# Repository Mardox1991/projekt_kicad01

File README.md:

# projekt_kicad01
4 layer universal pcb atmega328p ( first pcb project )

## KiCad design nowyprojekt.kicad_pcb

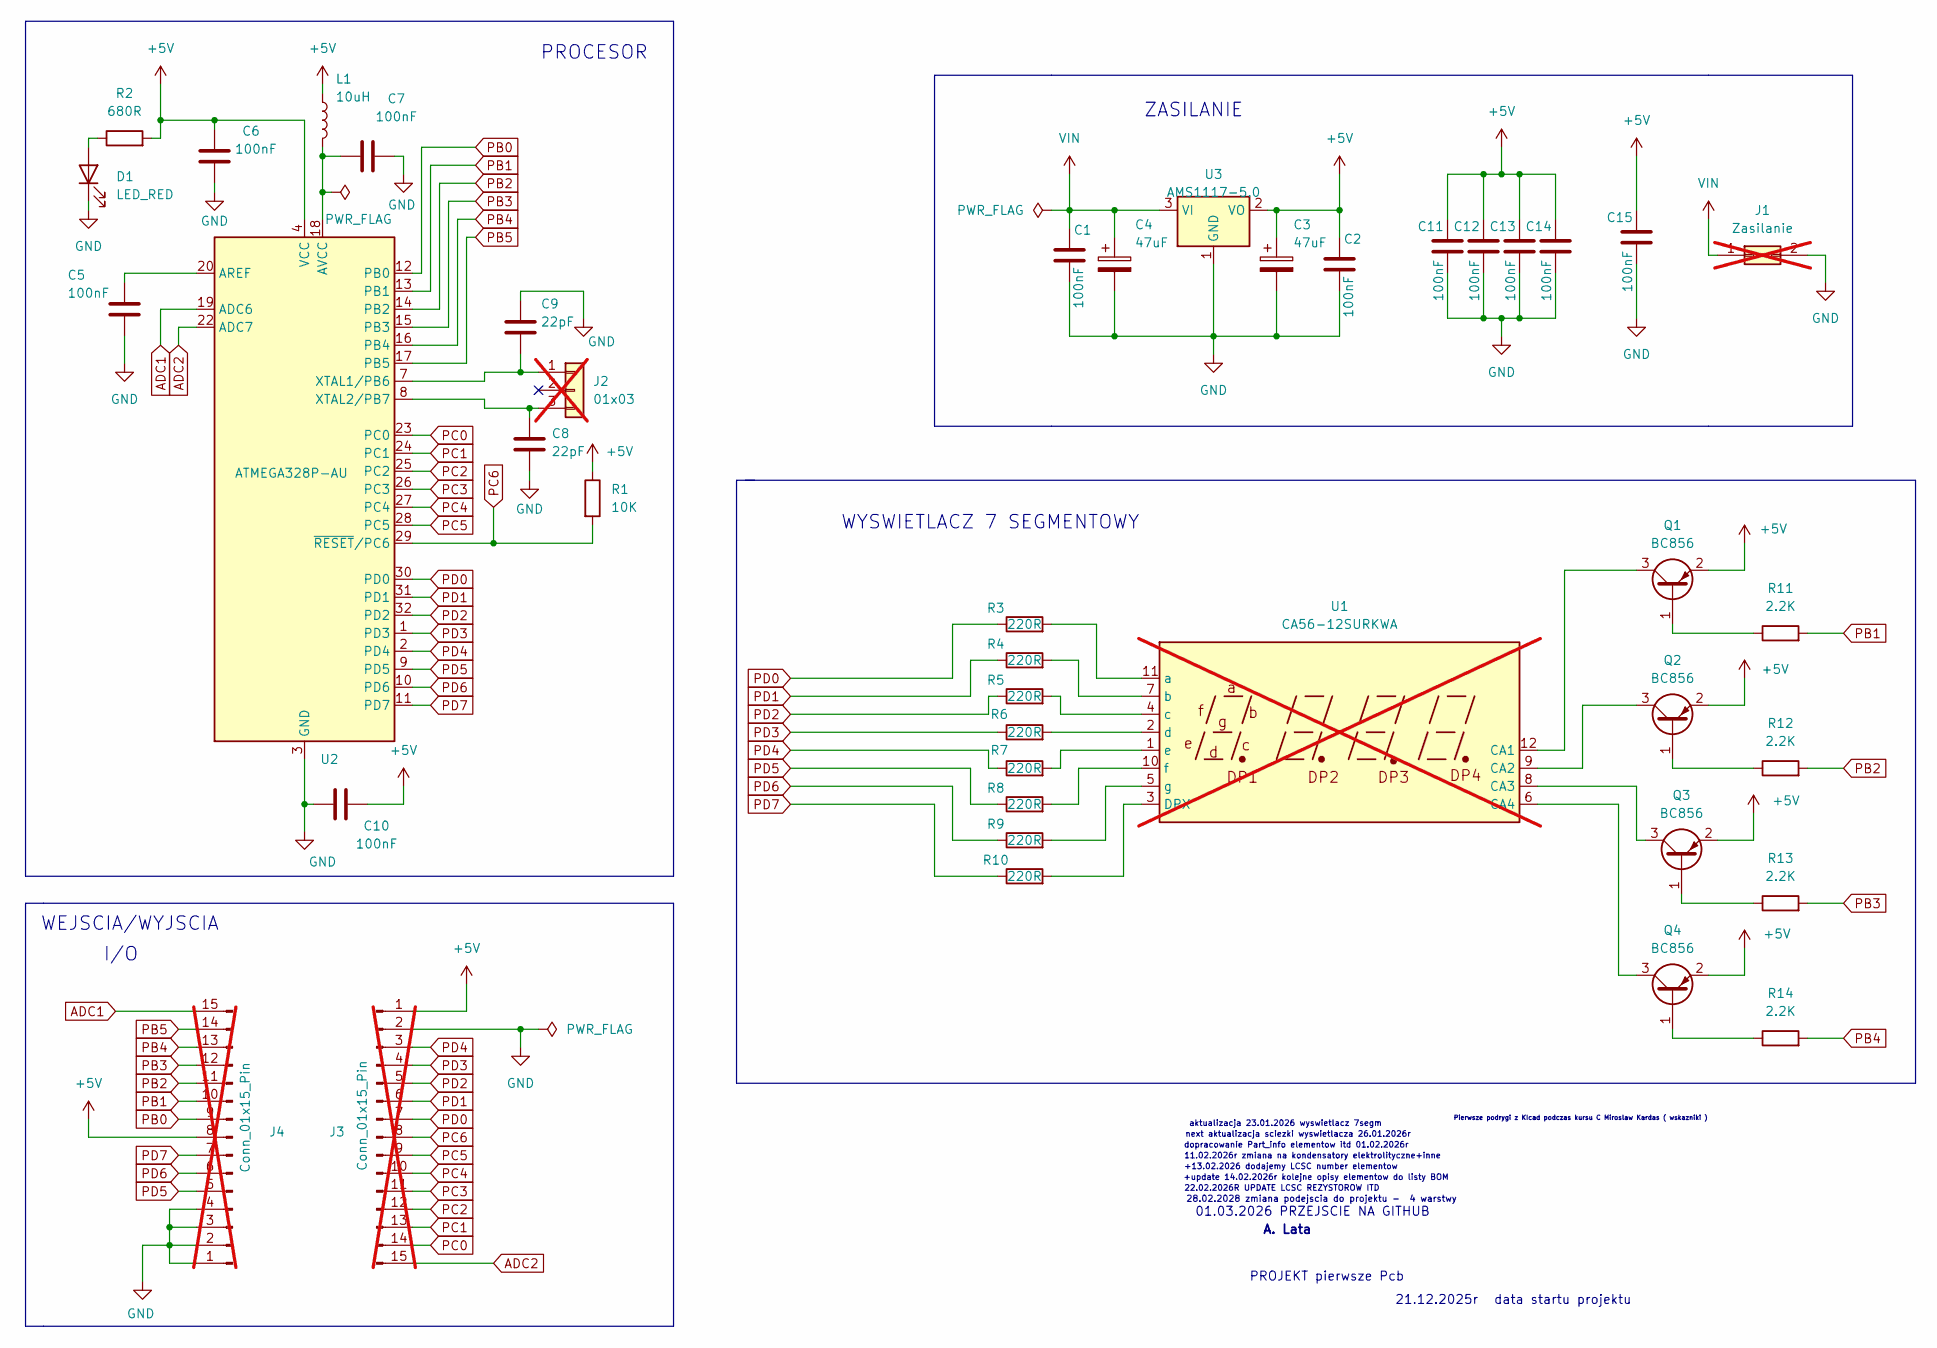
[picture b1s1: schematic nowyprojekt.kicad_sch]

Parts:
C1, C2, C5, C6, C7, C10, C11, C12, C13, C14, C15: 100nF; C_0603_1608Metric; Part_info Ceramic Capacitor 100nF 50V X7R 10%; LCSC C14663
C3, C4: 47uF; CP_Elec_8x6.2; Part_info 47µF, Low ESR, 50V DC, ±20%, -55...105°C; LCSC C278400
C8, C9: 22pF; C_0603_1608Metric; Part_info Ceramic Capacitor 22pF 50V C0G (NP0) 5%; LCSC C1653
D1: LED_RED; LED_0603_1608Metric; Part_info 20mA, 0603, Red, 2.4V, SMD; LCSC C2286
J1: Zasilanie; PinHeader_1x02_P2.54mm_Vertical; not fitted
J2: 01x03; PinHeader_1x03_P2.54mm_Vertical; not fitted
J3, J4: Conn_01x15_Pin; PinHeader_1x15_P2.54mm_Vertical; not fitted
L1: 10uH; L_1206_3216Metric; MPN CMP321609XD100MT; LCSC C395029
Q1, Q2, Q3, Q4: BC856; SOT-23; Part_info PNP, 65V, 0,1A, 0,25W, SMD; LCSC C108440
R1: 10K; R_0603_1608Metric; Part_info 10K, 0603, 1%, 0.1W, 75V; LCSC C25804
R2: 680R; R_0603_1608Metric; Part_info 0603, 680R, 1%, 0.1W, 75V; LCSC C23228
R3, R4, R5, R6, R7, R8, R9, R10: 220R; R_0603_1608Metric; Part_info 220R, 0603, 1%, 0.1W, 75V; LCSC C22962
R11, R12, R13, R14: 2.2K; R_0603_1608Metric; Part_info 2.2K, 0603, 1%, 0.1W, 75V; LCSC C4190
U1: CA56-12SURKWA; not fitted
U2: ATMEGA328P-AU; TQFP-32_7x7mm_P0.8mm; Part_info 20MHz, 32kB Flash, 2kB SRAM, 1kB EEPROM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; LCSC C14877
U3: AMS1117-5.0; SOT-223-3_TabPin2; Part_info 15Vsupply, 1A, 5V out; LCSC C6187

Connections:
+5V: C2.1, C3.1, C6.1, C10.2, C11.1, C12.1, C13.1, C14.1, C15.1, J3.1, J4.8, L1.1, Q1.2 (E), Q2.2 (E), Q3.2 (E), Q4.2 (E), R1.1, R2.2, U2.4 (VCC), U2.6 (VCC), U3.2 (VO)
ADC1: J4.15, U2.19 (ADC6)
ADC2: J3.15, U2.22 (ADC7)
GND: C1.2, C2.2, C3.2, C4.2, C5.2, C6.2, C7.2, C8.2, C9.1, C10.1, C11.2, C12.2, C13.2, C14.2, C15.2, D1.1 (K), J1.2, J3.2, J4.1, J4.2, J4.3, J4.4, U2.3 (GND), U2.5 (GND), U2.21 (GND), U3.1 (GND)
unnamed: D1.2 (A), R2.1
unnamed: C9.2, J2.1, U2.7 (XTAL1/PB6)
unnamed: C8.1, J2.3, U2.8 (XTAL2/PB7)
unnamed: Q1.1 (B), R11.1
unnamed: Q1.3 (C), U1.12 (CA1)
unnamed: Q2.1 (B), R12.1
unnamed: Q2.3 (C), U1.9 (CA2)
unnamed: Q3.1 (B), R13.1
unnamed: Q3.3 (C), U1.8 (CA3)
unnamed: Q4.1 (B), R14.1
unnamed: Q4.3 (C), U1.6 (CA4)
unnamed: R10.2, U1.3 (DPX)
unnamed: R3.2, U1.11 (a)
unnamed: R4.2, U1.7 (b)
unnamed: R5.2, U1.4 (c)
unnamed: R6.2, U1.2 (d)
unnamed: R7.2, U1.1 (e)
unnamed: R8.2, U1.10 (f)
unnamed: R9.2, U1.5 (g)
unnamed: C5.1, U2.20 (AREF)
unnamed: C7.1, L1.2, U2.18 (AVCC)
PB0: J4.9, U2.12 (PB0)
PB1: J4.10, R11.2, U2.13 (PB1)
PB2: J4.11, R12.2, U2.14 (PB2)
PB3: J4.12, R13.2, U2.15 (PB3)
PB4: J4.13, R14.2, U2.16 (PB4)
PB5: J4.14, U2.17 (PB5)
PC0: J3.14, U2.23 (PC0)
PC1: J3.13, U2.24 (PC1)
PC2: J3.12, U2.25 (PC2)
PC3: J3.11, U2.26 (PC3)
PC4: J3.10, U2.27 (PC4)
PC5: J3.9, U2.28 (PC5)
PC6: J3.8, R1.2, U2.29 (~RESET/PC6)
PD0: J3.7, R3.1, U2.30 (PD0)
PD1: J3.6, R4.1, U2.31 (PD1)
PD2: J3.5, R5.1, U2.32 (PD2)
PD3: J3.4, R6.1, U2.1 (PD3)
PD4: J3.3, R7.1, U2.2 (PD4)
PD5: J4.5, R8.1, U2.9 (PD5)
PD6: J4.6, R9.1, U2.10 (PD6)
PD7: J4.7, R10.1, U2.11 (PD7)
VIN: C1.1, C4.1, J1.1, U3.3 (VI)

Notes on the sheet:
A. Lata
PROCESOR
01.03.2026 PRZEJSCIE NA GITHUB
WYSWIETLACZ 7 SEGMENTOWY
dopracowanie Part_info elementow itd 01.02.2026r
next aktualizacja sciezki wyswietlacza 26.01.2026r
Pierwsze podrygi z KIcad podczas kursu C Miroslaw Kardas ( wskazniki )
ZASILANIE
data startu projektu
28.02.2028 zmiana podejscia do projektu - 4 warstwy
+update 14.02.2026r kolejne opisy elementow do listy BOM
21.12.2025r
PROJEKT pierwsze Pcb
I/O
WEJSCIA/WYJSCIA
11.02.2026r zmiana na kondensatory elektrolityczne+inne
+13.02.2026 dodajemy LCSC number elementow
aktualizacja 23.01.2026 wyswietlacz 7segm
22.02.2026R UPDATE LCSC REZYSTOROW ITD

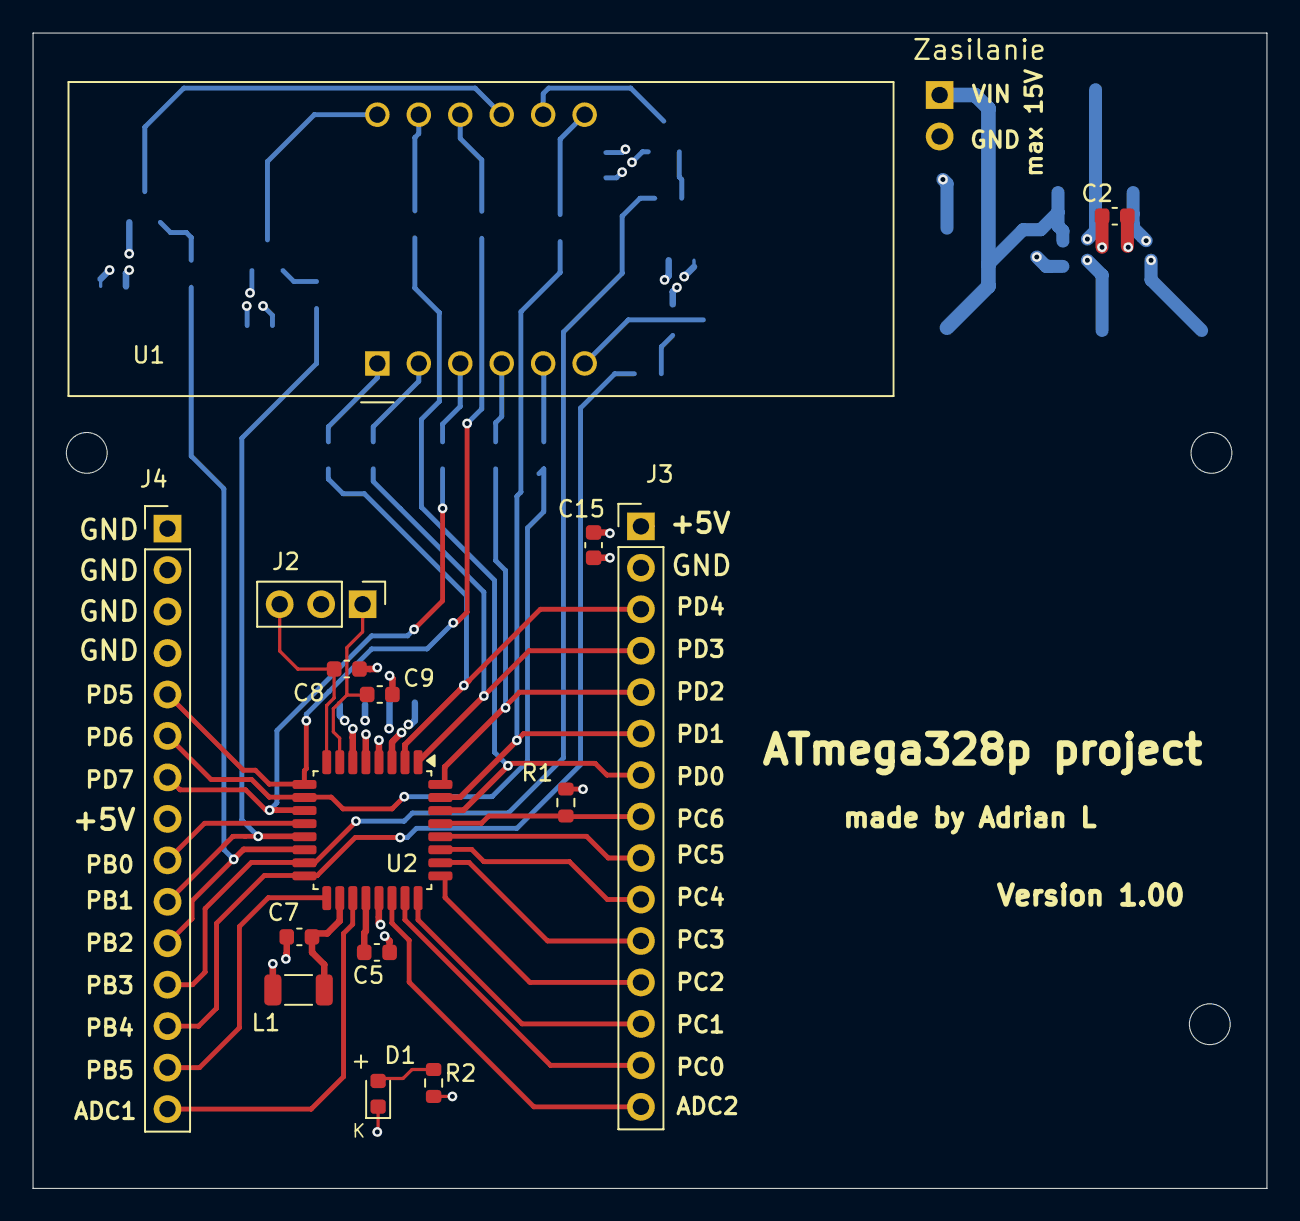
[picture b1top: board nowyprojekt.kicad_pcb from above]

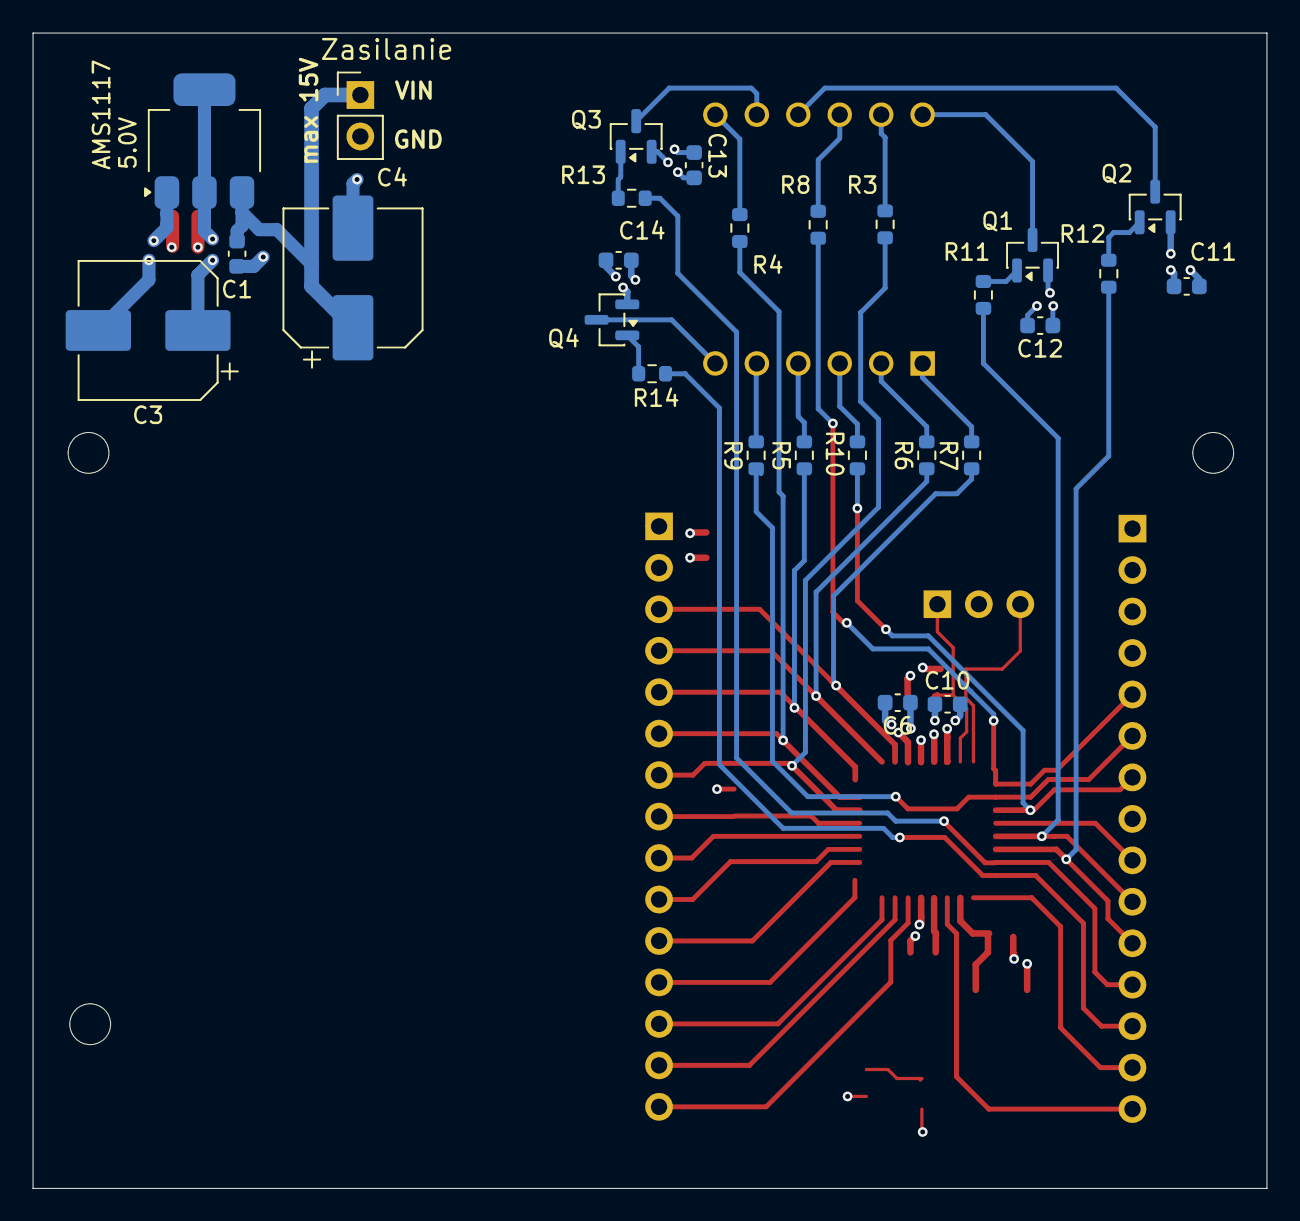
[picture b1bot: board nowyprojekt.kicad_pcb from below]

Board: 4 copper layers, 75.6 x 70.8 mm, 42 parts (27 on the bottom side), 47 nets.

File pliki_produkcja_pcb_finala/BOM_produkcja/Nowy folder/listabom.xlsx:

Reference | Qty | Value | DNP | Exclude from BOM | Exclude from Board | Footprint | Opis | MPN | Manufacturer | Part_info | LCSC
U3 | 1 | AMS1117-5.0 |  |  |  | Package_TO_SOT_SMD:SOT-223-3_TabPin2 | Low-Dropout Linear Regulator, 5.0V , SOT-223 | AMS1117-5.0 | Advanced Monolithic Systems | 15Vsupply, 1A, 5V out | C6187
U2 | 1 | ATMEGA328P-AU |  |  |  | Package_QFP:TQFP-32_7x7mm_P0.8mm | MICROCHIP ATMEGA328P-AU TQFP-32 SMD | ATMEGA328P-AU | MICROCHIP | 20MHz, 32kB Flash, 2kB SRAM, 1kB EEPROM, TQFP-32 | C14877
U1 | 1 | CA56-12SURKWA | DNP | Wyklucz z BOM |  | Display_7Segment:CA56-12SURKWA | 4 digit 7 segment hyper red LED, common anode
R11,R12,R13,R14 | 4 | 2.2K |  |  |  | Resistor_SMD:R_0603_1608Metric | Resistor | 0603WAF2201T5E | UNI-ROYAL | 2.2K, 0603, 1%, 0.1W, 75V | C4190
R3,R4,R5,R6,R7,R8,R9,R10 | 8 | 220R |  |  |  | Resistor_SMD:R_0603_1608Metric | Resistor | 0603WAF2200T5E | UNI-ROYAL | 220R, 0603, 1%, 0.1W, 75V | C22962
R2 | 1 | 680R |  |  |  | Resistor_SMD:R_0603_1608Metric | Resistor | 0603WAF6800T5E | UNI-ROYAL | 0603, 680R, 1%, 0.1W, 75V | C23228
R1 | 1 | 10K |  |  |  | Resistor_SMD:R_0603_1608Metric | Resistor | 0603WAF1002T5E | UNI-ROYAL | 10K, 0603, 1%, 0.1W, 75V | C25804
Q1,Q2,Q3,Q4 | 4 | BC856 |  |  |  | Package_TO_SOT_SMD:SOT-23 | 0.1A Ic, 65V Vce, PNP Transistor, SOT-23 | BC856,215 | NEXPERIA | PNP, 65V, 0,1A, 0,25W, SMD | C108440
L1 | 1 | 10uH |  |  |  | Inductor_SMD:L_1206_3216Metric | Inductor | CMP321609XD100MT | FH | 1206, 300mA, 10uH, 550mΩ, ±20% | C395029
J3,J4 | 2 | Conn_01x15_Pin | DNP | Wyklucz z BOM |  | Connector_PinHeader_2.54mm:PinHeader_1x15_P2.54mm_Vertical | Generic connector, single row, 01x15, script generated
J2 | 1 | 01x03 | DNP | Wyklucz z BOM |  | Connector_PinHeader_2.54mm:PinHeader_1x03_P2.54mm_Vertical | Generic connector, single row, 01x03, script generated (kicad-library-utils/sch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
J1 | 1 | Zasilanie | DNP | Wyklucz z BOM |  | Connector_PinHeader_2.54mm:PinHeader_1x02_P2.54mm_Vertical | Generic connector, double row, 02x01, this symbol is compatible with counter-cl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
D1 | 1 | LED_RED |  |  |  | LED_SMD:LED_0603_1608Metric | Light emitting diode | KT-0603R | Hubei KENTO Elec | 20mA, 0603, Red, 2.4V, SMD | C2286
C8,C9 | 2 | 22pF |  |  |  | Capacitor_SMD:C_0603_1608Metric | Unpolarized capacitor | CL10C220JB8NNNC | SAMSUNG | Ceramic Capacitor 22pF 50V C0G (NP0) 5% | C1653
C3,C4 | 2 | 47uF |  |  |  | Capacitor_SMD:CP_Elec_8x6.2 | Polarized capacitor | EEEFK1H470P | PANASONIC | 47µF, Low ESR, 50V DC, ±20%, -55...105°C | C278400
C1,C2,C5,C6,C7,C10,C11,C12,C13,C14,C15 | 11 | 100nF |  |  |  | Capacitor_SMD:C_0603_1608Metric | Unpolarized capacitor | CC0603KRX7R9BB104 | YAGEO | Ceramic Capacitor 100nF 50V X7R 10% | C14663

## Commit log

2026-03-01 Pierwszy wrzut projektu pcb atmega328p
2026-03-01 Inne rozwiazanie prowadzenia sciezek, z mysleniem zgodnym z 4 warstwami plytki... przelotki zasilania stabilizatora obok przelotek kondensatorow itd
2026-03-01 dodanie do biblioteki kondensator 10nF
2026-03-01 01.03.2026r zmiana prowadzenia sciezek - myslenie pod 4 warstwowe pcb
2026-03-01 01.03.2026r zmiana prowadzenia sciezek - myslenie pod 4 warstwowe pcb czesc 2 - zakonczenie
2026-03-02 maly update02.03.2026r
2026-03-06 06.03.2026 small update
2026-03-06 biggest update 06.03.2026r
2026-03-07 07.03.2026r update LISTA BOM itd
2026-03-14 14.03.2026r walka z generowaniem plikow dla jlcpcb
2026-04-04 latest 04.04.2026r update - text - opis PCB
2026-04-04 latest update 04.04.2026 finally - opis PCB
